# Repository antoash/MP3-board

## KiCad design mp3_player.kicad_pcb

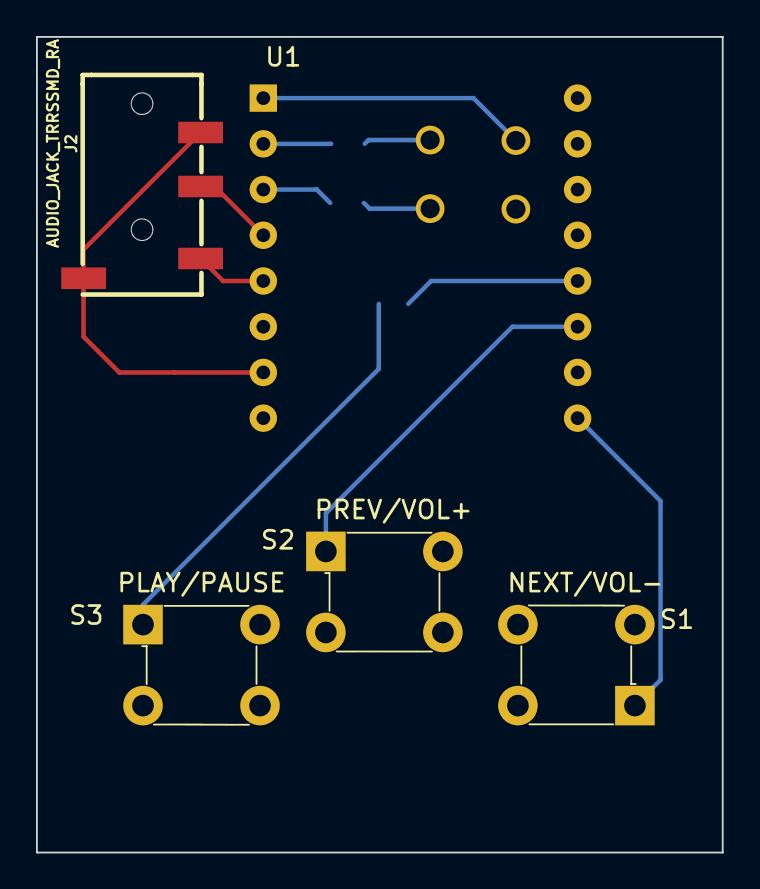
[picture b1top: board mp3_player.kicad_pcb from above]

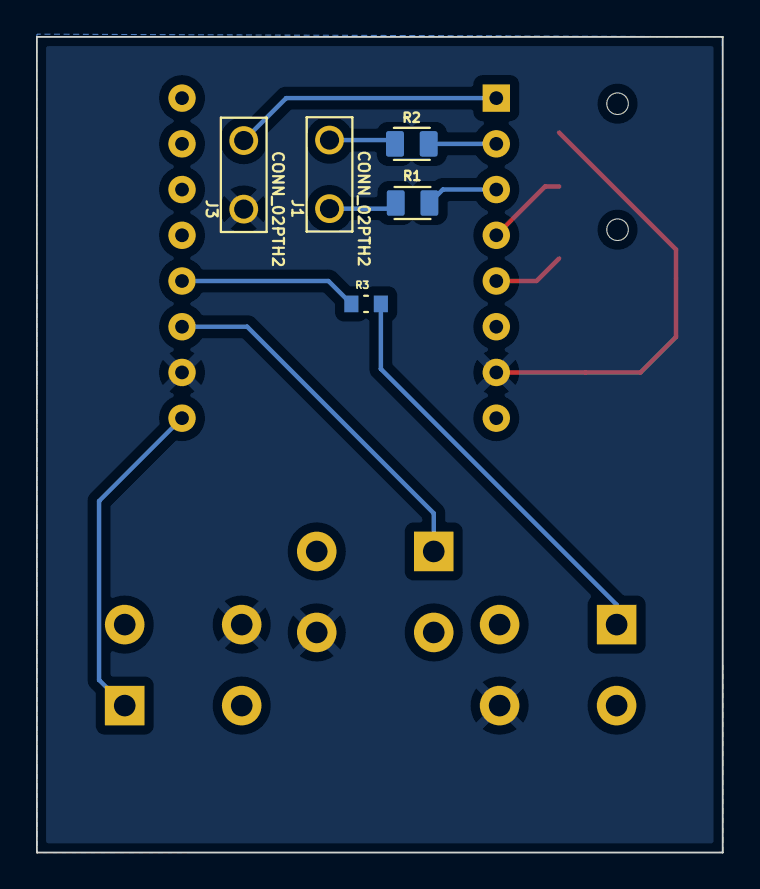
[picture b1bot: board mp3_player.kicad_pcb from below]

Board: 2 copper layers, 38.1 x 45.3 mm, 10 parts (5 on the bottom side), 12 nets.

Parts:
J1, J3: CONN_02PTH2; 1X02_BIG
J2: AUDIO_JACK_TRRSSMD_RA; AUDIO_JACK_3.5MM_TRRS_SMD_RA
R1, R2: 1k; RESC2012X65N
R3: 33k; RESC1608X55N
S1, S2, S3: 1825910-6; Switch_Tactile_THT_6x6mm
U1: DFPLAYER_MINI; DF_PlayerMini

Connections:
GND: J2.EART (EARTH), J2.RING (RING2), J3.P$1, S1.4, S2.4, S3.4, U1.7 (GND), U1.10 (GND)
unnamed: J1.P$1, R1.1
unnamed: J1.P$2, R2.1
unnamed: J2.RING (RING2), U1.4 (DAC-R)
unnamed: J2.TIP, U1.5 (DAC-L)
unnamed: R1.2, U1.3 (TX)
unnamed: R2.2, U1.2 (RX)
unnamed: R3.1, U1.12 (KEY1)
unnamed: R3.2, S3.1
unnamed: S1.1, U1.9 (IO1)
unnamed: S2.1, U1.11 (IO2)
POWER: J3.P$2, U1.1 (VCC)

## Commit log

2024-12-09 Add files
2024-12-09 Add images
